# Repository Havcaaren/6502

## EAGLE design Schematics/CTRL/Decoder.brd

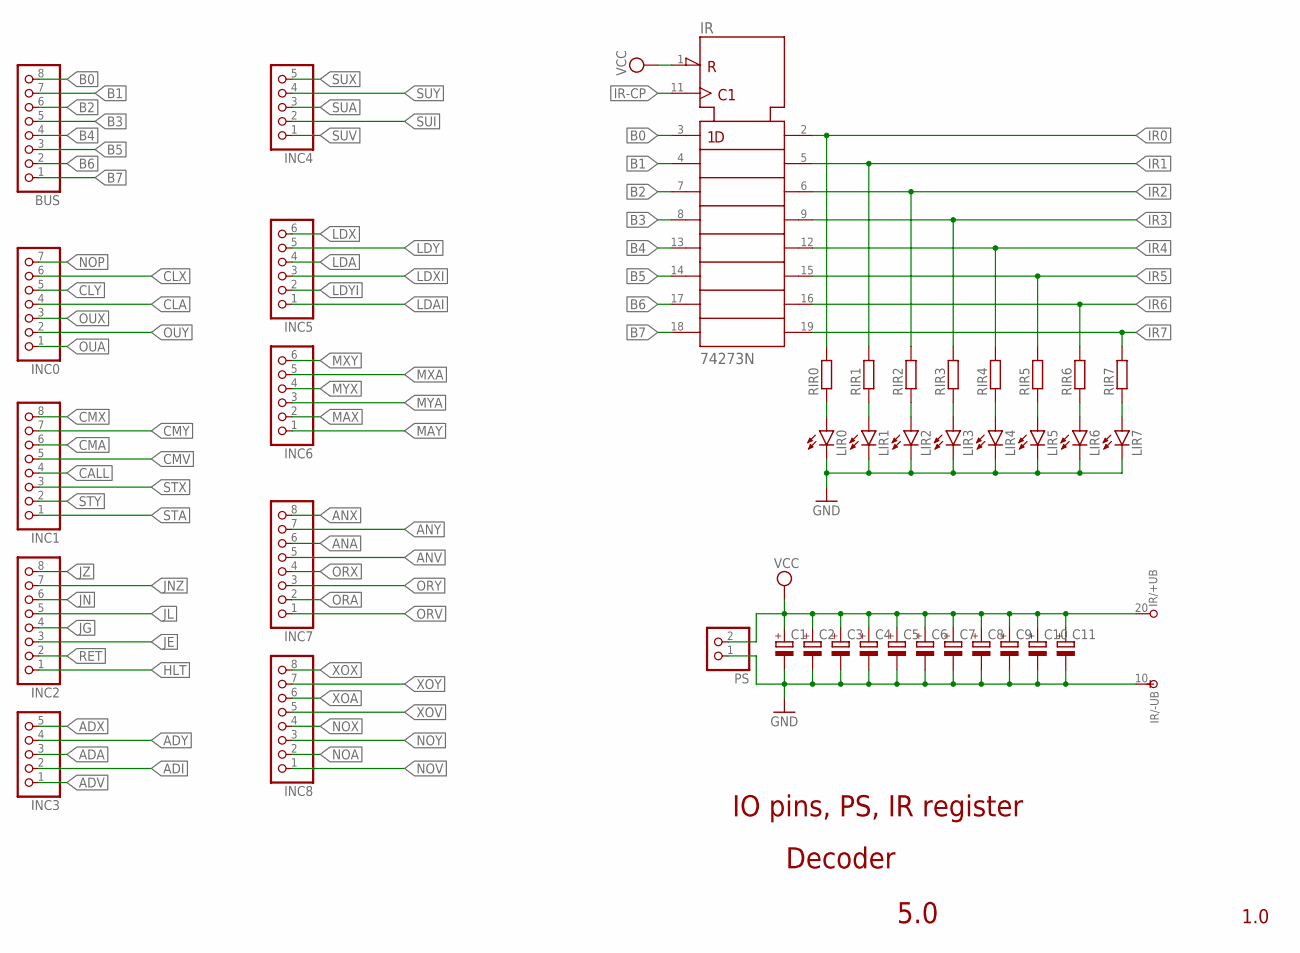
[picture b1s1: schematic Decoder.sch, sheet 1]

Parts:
BUS: PINHD-1X8; 1X08
C1, C2, C3, C4, C5, C6, C7, C8, C9, C10, C11: CPOL-EUE2.5-6; E2,5-6
INC0: PINHD-1X7; 1X07
INC1, INC2, INC7, INC8: PINHD-1X8; 1X08
INC3, INC4: PINHD-1X5; 1X05
INC5, INC6: PINHD-1X6; 1X06
IR: 74273N; DIL20
LIR0, LIR1, LIR2, LIR3, LIR4, LIR5, LIR6, LIR7: LED5MM
PS: PINHD-1X2; 1X02
RIR0, RIR1, RIR2, RIR3, RIR4, RIR5, RIR6, RIR7: R-EU_0204/7; 0204/7

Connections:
ADA: INC3.3; also elsewhere on the board
ADI: INC3.2; also elsewhere on the board
ADV: INC3.1; also elsewhere on the board
ADX: INC3.5; also elsewhere on the board
ADY: INC3.4; also elsewhere on the board
ANA: INC7.6; also elsewhere on the board
ANV: INC7.5; also elsewhere on the board
ANX: INC7.8; also elsewhere on the board
ANY: INC7.7; also elsewhere on the board
B0: BUS.8, IR.3 (1D)
B1: BUS.7, IR.4 (2D)
B2: BUS.6, IR.7 (3D)
B3: BUS.5, IR.8 (4D)
B4: BUS.4, IR.13 (5D)
B5: BUS.3, IR.14 (6D)
B6: BUS.2, IR.17 (7D)
B7: BUS.1, IR.18 (8D)
CALL: INC1.4; also elsewhere on the board
CLA: INC0.4; also elsewhere on the board
CLX: INC0.6; also elsewhere on the board
CLY: INC0.5; also elsewhere on the board
CMA: INC1.6; also elsewhere on the board
CMV: INC1.5; also elsewhere on the board
CMX: INC1.8; also elsewhere on the board
CMY: INC1.7; also elsewhere on the board
GND: C1.-, C2.-, C3.-, C4.-, C5.-, C6.-, C7.-, C8.-, C9.-, C10.-, C11.-, IR.10 (-UB), LIR0.K (C), LIR1.K (C), LIR2.K (C), LIR3.K (C), LIR4.K (C), LIR5.K (C), LIR6.K (C), LIR7.K (C), PS.1; also elsewhere on the board
HLT: INC2.1; also elsewhere on the board
IR0: IR.2 (1Q), RIR0.2; also elsewhere on the board
IR1: IR.5 (2Q), RIR1.2; also elsewhere on the board
IR2: IR.6 (3Q), RIR2.2; also elsewhere on the board
IR3: IR.9 (4Q), RIR3.2; also elsewhere on the board
IR4: IR.12 (5Q), RIR4.2; also elsewhere on the board
IR5: IR.15 (6Q), RIR5.2; also elsewhere on the board
IR6: IR.16 (7Q), RIR6.2; also elsewhere on the board
IR7: IR.19 (8Q), RIR7.2; also elsewhere on the board
IR-CP: IR.11 (CLK); also elsewhere on the board
JE: INC2.3; also elsewhere on the board
JG: INC2.4; also elsewhere on the board
JL: INC2.5; also elsewhere on the board
JN: INC2.6; also elsewhere on the board
JNZ: INC2.7; also elsewhere on the board
JZ: INC2.8; also elsewhere on the board
LDA: INC5.4; also elsewhere on the board
LDAI: INC5.1; also elsewhere on the board
LDX: INC5.6; also elsewhere on the board
LDXI: INC5.3; also elsewhere on the board
LDY: INC5.5; also elsewhere on the board
LDYI: INC5.2; also elsewhere on the board
MAX: INC6.2; also elsewhere on the board
MAY: INC6.1; also elsewhere on the board
MXA: INC6.5; also elsewhere on the board
MXY: INC6.6; also elsewhere on the board
MYA: INC6.3; also elsewhere on the board
MYX: INC6.4; also elsewhere on the board
unnamed: LIR0.A, RIR0.1
unnamed: LIR1.A, RIR1.1
unnamed: LIR2.A, RIR2.1
unnamed: LIR3.A, RIR3.1
unnamed: LIR4.A, RIR4.1
unnamed: LIR5.A, RIR5.1
unnamed: LIR6.A, RIR6.1
unnamed: LIR7.A, RIR7.1
NOA: INC8.2; also elsewhere on the board
NOP: INC0.7; also elsewhere on the board
NOV: INC8.1; also elsewhere on the board
NOX: INC8.4; also elsewhere on the board
NOY: INC8.3; also elsewhere on the board
ORA: INC7.2; also elsewhere on the board
ORV: INC7.1; also elsewhere on the board
ORX: INC7.4; also elsewhere on the board
ORY: INC7.3; also elsewhere on the board
OUA: INC0.1; also elsewhere on the board
OUX: INC0.3; also elsewhere on the board
OUY: INC0.2; also elsewhere on the board
RET: INC2.2; also elsewhere on the board
STA: INC1.1; also elsewhere on the board
STX: INC1.3; also elsewhere on the board
STY: INC1.2; also elsewhere on the board
SUA: INC4.3; also elsewhere on the board
SUI: INC4.2; also elsewhere on the board
SUV: INC4.1; also elsewhere on the board
SUX: INC4.5; also elsewhere on the board
SUY: INC4.4; also elsewhere on the board
VCC: C1.+, C2.+, C3.+, C4.+, C5.+, C6.+, C7.+, C8.+, C9.+, C10.+, C11.+, IR.1 (!CLR), IR.20 (+UB), PS.2; also elsewhere on the board
XOA: INC8.6; also elsewhere on the board
XOV: INC8.5; also elsewhere on the board
XOX: INC8.8; also elsewhere on the board
XOY: INC8.7; also elsewhere on the board

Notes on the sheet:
1.0
5.0
Decoder
IO pins, PS, IR register

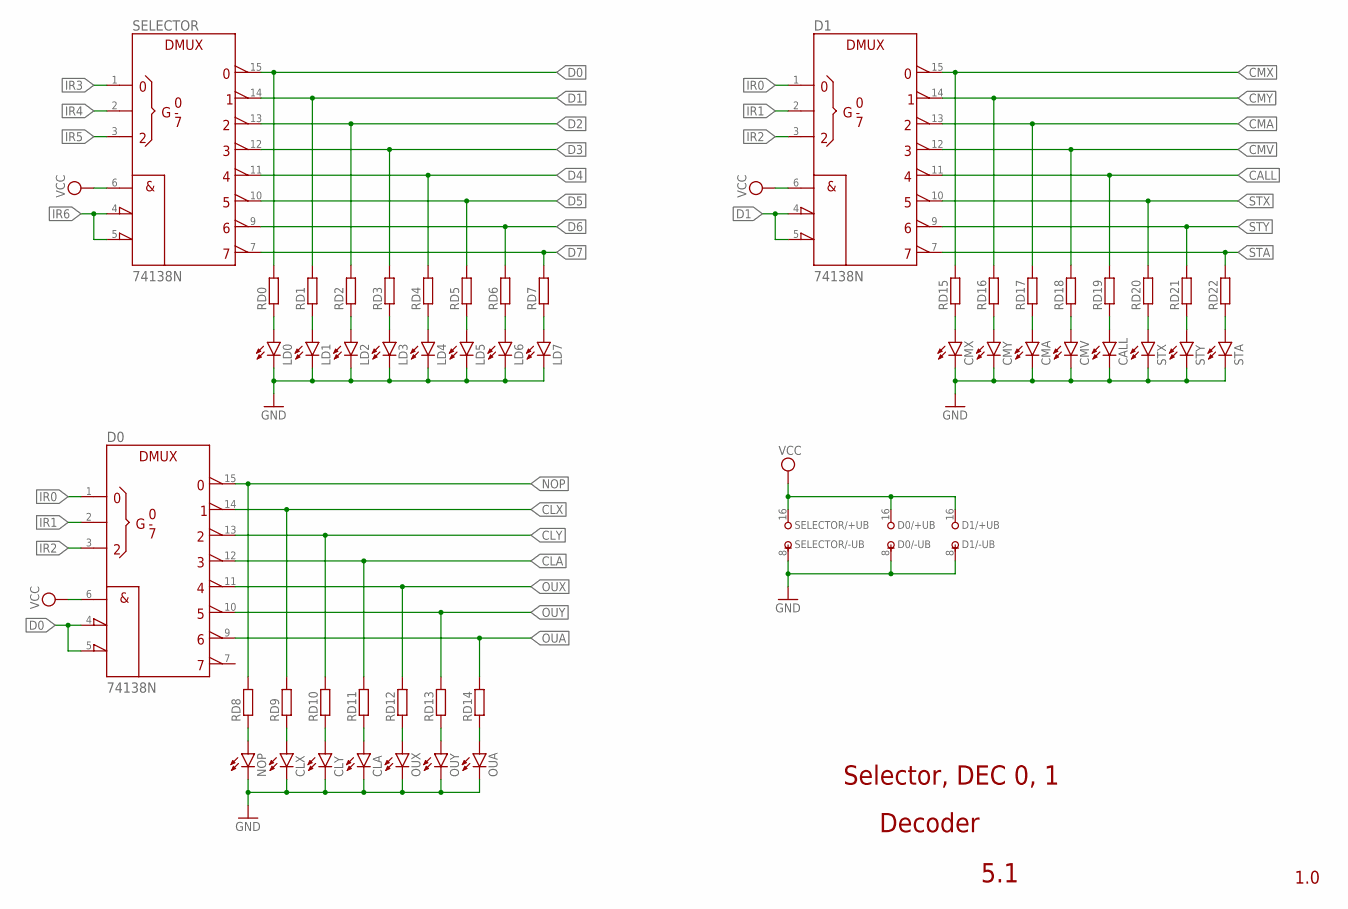
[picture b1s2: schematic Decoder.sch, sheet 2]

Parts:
CALL: LED5MM
CLA: LED5MM
CLX: LED5MM
CLY: LED5MM
CMA: LED5MM
CMV: LED5MM
CMX: LED5MM
CMY: LED5MM
D0, D1: 74138N; DIL16
LD0, LD1, LD2, LD3, LD4, LD5, LD6, LD7: LED5MM
NOP: LED5MM
OUA: LED5MM
OUX: LED5MM
OUY: LED5MM
RD0, RD1, RD2, RD3, RD4, RD5, RD6, RD7, RD8, RD9, RD10, RD11, RD12, RD13, RD14, RD15, RD16, RD17, RD18, RD19, RD20, RD21, RD22: R-EU_0204/7; 0204/7
SELECTOR: 74138N; DIL16
STA: LED5MM
STX: LED5MM
STY: LED5MM

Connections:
CALL: D1.11 (Y4), RD19.2; also elsewhere on the board
CLA: D0.12 (Y3), RD11.2; also elsewhere on the board
CLX: D0.14 (Y1), RD9.2; also elsewhere on the board
CLY: D0.13 (Y2), RD10.2; also elsewhere on the board
CMA: D1.13 (Y2), RD17.2; also elsewhere on the board
CMV: D1.12 (Y3), RD18.2; also elsewhere on the board
CMX: D1.15 (Y0), RD15.2; also elsewhere on the board
CMY: D1.14 (Y1), RD16.2; also elsewhere on the board
D0: D0.4 (!G2A), D0.5 (!G2B), RD0.2, SELECTOR.15 (Y0)
D1: D1.4 (!G2A), D1.5 (!G2B), RD1.2, SELECTOR.14 (Y1)
D2: RD2.2, SELECTOR.13 (Y2); also elsewhere on the board
D3: RD3.2, SELECTOR.12 (Y3); also elsewhere on the board
D4: RD4.2, SELECTOR.11 (Y4); also elsewhere on the board
D5: RD5.2, SELECTOR.10 (Y5); also elsewhere on the board
D6: RD6.2, SELECTOR.9 (Y6); also elsewhere on the board
D7: RD7.2, SELECTOR.7 (Y7); also elsewhere on the board
GND: CALL.K (C), CLA.K (C), CLX.K (C), CLY.K (C), CMA.K (C), CMV.K (C), CMX.K (C), CMY.K (C), D0.8 (-UB), D1.8 (-UB), LD0.K (C), LD1.K (C), LD2.K (C), LD3.K (C), LD4.K (C), LD5.K (C), LD6.K (C), LD7.K (C), NOP.K (C), OUA.K (C), OUX.K (C), OUY.K (C), SELECTOR.8 (-UB), STA.K (C), STX.K (C), STY.K (C); also elsewhere on the board
IR0: D0.1 (A), D1.1 (A); also elsewhere on the board
IR1: D0.2 (B), D1.2 (B); also elsewhere on the board
IR2: D0.3 (C), D1.3 (C); also elsewhere on the board
IR3: SELECTOR.1 (A); also elsewhere on the board
IR4: SELECTOR.2 (B); also elsewhere on the board
IR5: SELECTOR.3 (C); also elsewhere on the board
IR6: SELECTOR.4 (!G2A), SELECTOR.5 (!G2B); also elsewhere on the board
unnamed: LD0.A, RD0.1
unnamed: LD1.A, RD1.1
unnamed: LD2.A, RD2.1
unnamed: LD3.A, RD3.1
unnamed: LD4.A, RD4.1
unnamed: LD5.A, RD5.1
unnamed: LD6.A, RD6.1
unnamed: LD7.A, RD7.1
unnamed: CMX.A, RD15.1
unnamed: CMY.A, RD16.1
unnamed: CMA.A, RD17.1
unnamed: CMV.A, RD18.1
unnamed: CALL.A, RD19.1
unnamed: RD20.1, STX.A
unnamed: RD21.1, STY.A
unnamed: RD22.1, STA.A
unnamed: NOP.A, RD8.1
unnamed: CLX.A, RD9.1
unnamed: CLY.A, RD10.1
unnamed: CLA.A, RD11.1
unnamed: OUX.A, RD12.1
unnamed: OUY.A, RD13.1
unnamed: OUA.A, RD14.1
NOP: D0.15 (Y0), RD8.2; also elsewhere on the board
OUA: D0.9 (Y6), RD14.2; also elsewhere on the board
OUX: D0.11 (Y4), RD12.2; also elsewhere on the board
OUY: D0.10 (Y5), RD13.2; also elsewhere on the board
STA: D1.7 (Y7), RD22.2; also elsewhere on the board
STX: D1.10 (Y5), RD20.2; also elsewhere on the board
STY: D1.9 (Y6), RD21.2; also elsewhere on the board
VCC: D0.6 (G1), D0.16 (+UB), D1.6 (G1), D1.16 (+UB), SELECTOR.6 (G1), SELECTOR.16 (+UB); also elsewhere on the board

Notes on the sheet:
Decoder
5.1
1.0
Selector, DEC 0, 1

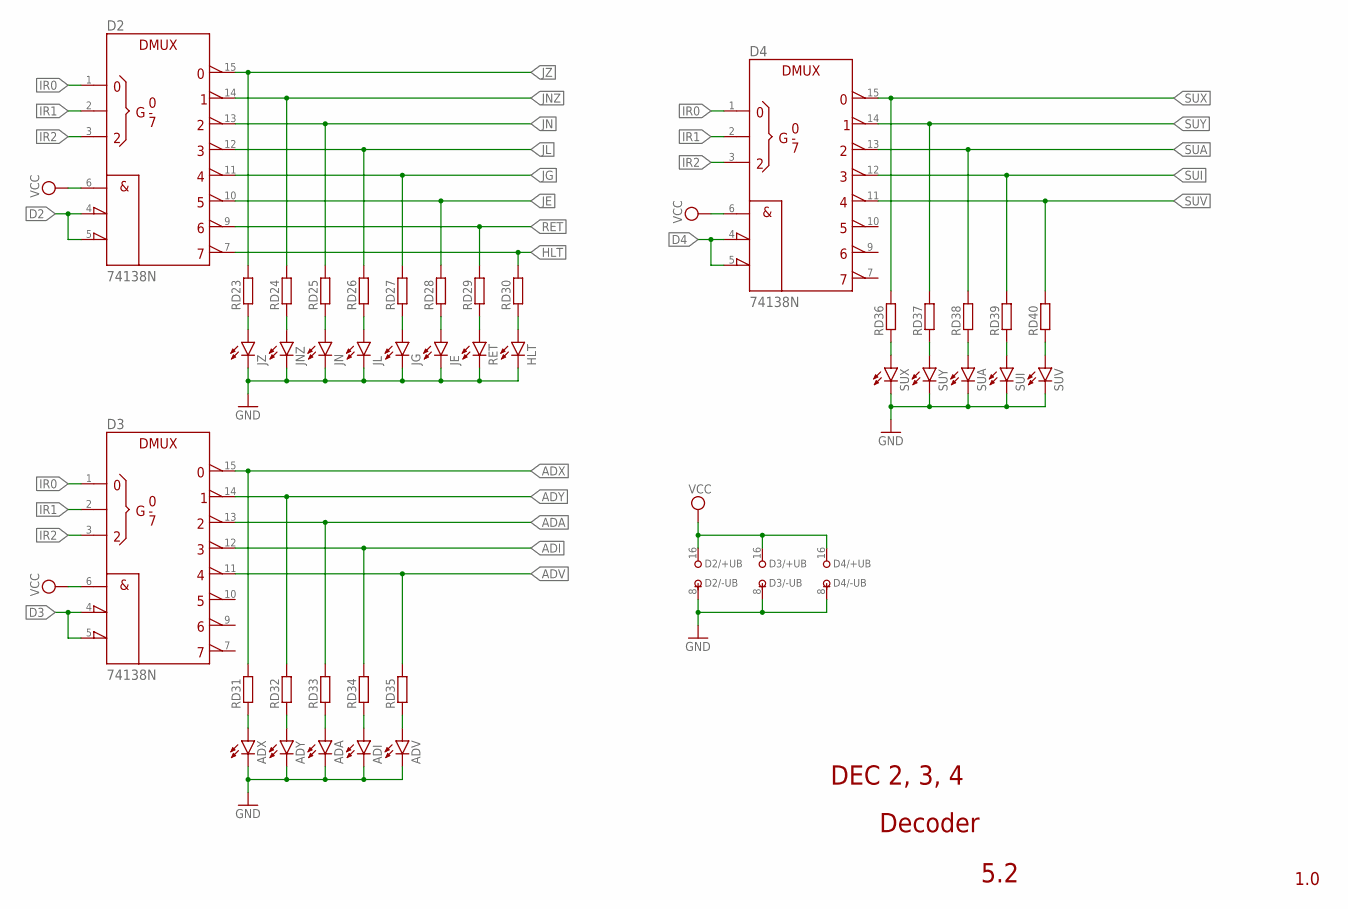
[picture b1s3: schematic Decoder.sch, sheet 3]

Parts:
ADA: LED5MM
ADI: LED5MM
ADV: LED5MM
ADX: LED5MM
ADY: LED5MM
D2, D3, D4: 74138N; DIL16
HLT: LED5MM
JE: LED5MM
JG: LED5MM
JL: LED5MM
JN: LED5MM
JNZ: LED5MM
JZ: LED5MM
RD23, RD24, RD25, RD26, RD27, RD28, RD29, RD30, RD31, RD32, RD33, RD34, RD35, RD36, RD37, RD38, RD39, RD40: R-EU_0204/7; 0204/7
RET: LED5MM
SUA: LED5MM
SUI: LED5MM
SUV: LED5MM
SUX: LED5MM
SUY: LED5MM

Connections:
ADA: D3.13 (Y2), RD33.2; also elsewhere on the board
ADI: D3.12 (Y3), RD34.2; also elsewhere on the board
ADV: D3.11 (Y4), RD35.2; also elsewhere on the board
ADX: D3.15 (Y0), RD31.2; also elsewhere on the board
ADY: D3.14 (Y1), RD32.2; also elsewhere on the board
D2: D2.4 (!G2A), D2.5 (!G2B); also elsewhere on the board
D3: D3.4 (!G2A), D3.5 (!G2B); also elsewhere on the board
D4: D4.4 (!G2A), D4.5 (!G2B); also elsewhere on the board
GND: ADA.K (C), ADI.K (C), ADV.K (C), ADX.K (C), ADY.K (C), D2.8 (-UB), D3.8 (-UB), D4.8 (-UB), HLT.K (C), JE.K (C), JG.K (C), JL.K (C), JN.K (C), JNZ.K (C), JZ.K (C), RET.K (C), SUA.K (C), SUI.K (C), SUV.K (C), SUX.K (C), SUY.K (C); also elsewhere on the board
HLT: D2.7 (Y7), RD30.2; also elsewhere on the board
IR0: D2.1 (A), D3.1 (A), D4.1 (A); also elsewhere on the board
IR1: D2.2 (B), D3.2 (B), D4.2 (B); also elsewhere on the board
IR2: D2.3 (C), D3.3 (C), D4.3 (C); also elsewhere on the board
JE: D2.10 (Y5), RD28.2; also elsewhere on the board
JG: D2.11 (Y4), RD27.2; also elsewhere on the board
JL: D2.12 (Y3), RD26.2; also elsewhere on the board
JN: D2.13 (Y2), RD25.2; also elsewhere on the board
JNZ: D2.14 (Y1), RD24.2; also elsewhere on the board
JZ: D2.15 (Y0), RD23.2; also elsewhere on the board
unnamed: JZ.A, RD23.1
unnamed: JNZ.A, RD24.1
unnamed: JN.A, RD25.1
unnamed: JL.A, RD26.1
unnamed: JG.A, RD27.1
unnamed: JE.A, RD28.1
unnamed: RD29.1, RET.A
unnamed: HLT.A, RD30.1
unnamed: ADX.A, RD31.1
unnamed: ADY.A, RD32.1
unnamed: ADA.A, RD33.1
unnamed: ADI.A, RD34.1
unnamed: ADV.A, RD35.1
unnamed: RD36.1, SUX.A
unnamed: RD37.1, SUY.A
unnamed: RD38.1, SUA.A
unnamed: RD39.1, SUI.A
unnamed: RD40.1, SUV.A
RET: D2.9 (Y6), RD29.2; also elsewhere on the board
SUA: D4.13 (Y2), RD38.2; also elsewhere on the board
SUI: D4.12 (Y3), RD39.2; also elsewhere on the board
SUV: D4.11 (Y4), RD40.2; also elsewhere on the board
SUX: D4.15 (Y0), RD36.2; also elsewhere on the board
SUY: D4.14 (Y1), RD37.2; also elsewhere on the board
VCC: D2.6 (G1), D2.16 (+UB), D3.6 (G1), D3.16 (+UB), D4.6 (G1), D4.16 (+UB); also elsewhere on the board

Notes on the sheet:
Decoder
5.2
1.0
DEC 2, 3, 4

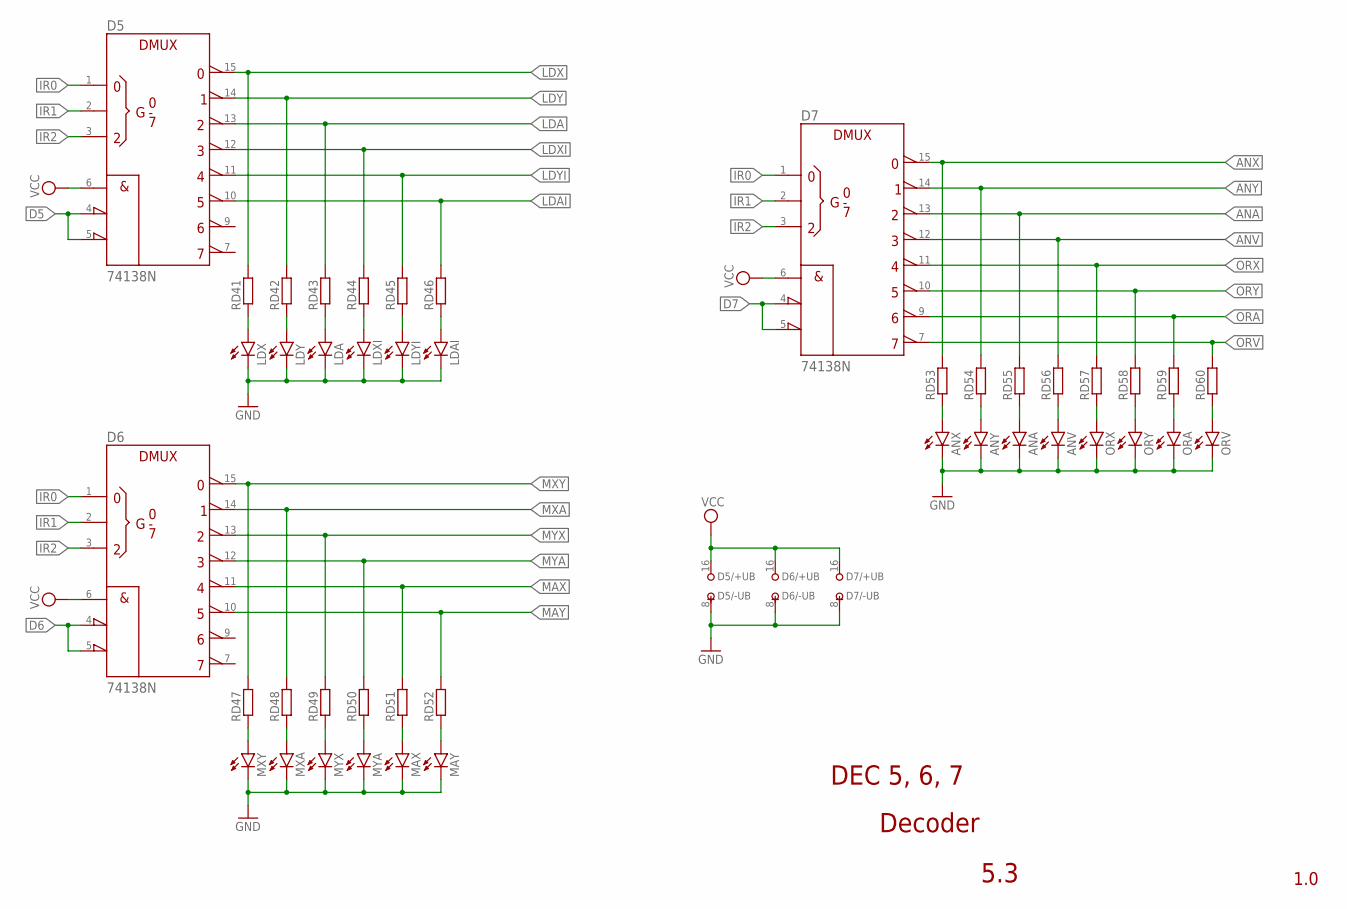
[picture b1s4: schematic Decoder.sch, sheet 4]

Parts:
ANA: LED5MM
ANV: LED5MM
ANX: LED5MM
ANY: LED5MM
D5, D6, D7: 74138N; DIL16
LDA: LED5MM
LDAI: LED5MM
LDX: LED5MM
LDXI: LED5MM
LDY: LED5MM
LDYI: LED5MM
MAX: LED5MM
MAY: LED5MM
MXA: LED5MM
MXY: LED5MM
MYA: LED5MM
MYX: LED5MM
ORA: LED5MM
ORV: LED5MM
ORX: LED5MM
ORY: LED5MM
RD41, RD42, RD43, RD44, RD45, RD46, RD47, RD48, RD49, RD50, RD51, RD52, RD53, RD54, RD55, RD56, RD57, RD58, RD59, RD60: R-EU_0204/7; 0204/7

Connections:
ANA: D7.13 (Y2), RD55.2; also elsewhere on the board
ANV: D7.12 (Y3), RD56.2; also elsewhere on the board
ANX: D7.15 (Y0), RD53.2; also elsewhere on the board
ANY: D7.14 (Y1), RD54.2; also elsewhere on the board
D5: D5.4 (!G2A), D5.5 (!G2B); also elsewhere on the board
D6: D6.4 (!G2A), D6.5 (!G2B); also elsewhere on the board
D7: D7.4 (!G2A), D7.5 (!G2B); also elsewhere on the board
GND: ANA.K (C), ANV.K (C), ANX.K (C), ANY.K (C), D5.8 (-UB), D6.8 (-UB), D7.8 (-UB), LDA.K (C), LDAI.K (C), LDX.K (C), LDXI.K (C), LDY.K (C), LDYI.K (C), MAX.K (C), MAY.K (C), MXA.K (C), MXY.K (C), MYA.K (C), MYX.K (C), ORA.K (C), ORV.K (C), ORX.K (C), ORY.K (C); also elsewhere on the board
IR0: D5.1 (A), D6.1 (A), D7.1 (A); also elsewhere on the board
IR1: D5.2 (B), D6.2 (B), D7.2 (B); also elsewhere on the board
IR2: D5.3 (C), D6.3 (C), D7.3 (C); also elsewhere on the board
LDA: D5.13 (Y2), RD43.2; also elsewhere on the board
LDAI: D5.10 (Y5), RD46.2; also elsewhere on the board
LDX: D5.15 (Y0), RD41.2; also elsewhere on the board
LDXI: D5.12 (Y3), RD44.2; also elsewhere on the board
LDY: D5.14 (Y1), RD42.2; also elsewhere on the board
LDYI: D5.11 (Y4), RD45.2; also elsewhere on the board
MAX: D6.11 (Y4), RD51.2; also elsewhere on the board
MAY: D6.10 (Y5), RD52.2; also elsewhere on the board
MXA: D6.14 (Y1), RD48.2; also elsewhere on the board
MXY: D6.15 (Y0), RD47.2; also elsewhere on the board
MYA: D6.12 (Y3), RD50.2; also elsewhere on the board
MYX: D6.13 (Y2), RD49.2; also elsewhere on the board
unnamed: LDX.A, RD41.1
unnamed: LDY.A, RD42.1
unnamed: LDA.A, RD43.1
unnamed: LDXI.A, RD44.1
unnamed: LDYI.A, RD45.1
unnamed: LDAI.A, RD46.1
unnamed: MXY.A, RD47.1
unnamed: MXA.A, RD48.1
unnamed: MYX.A, RD49.1
unnamed: MYA.A, RD50.1
unnamed: MAX.A, RD51.1
unnamed: MAY.A, RD52.1
unnamed: ANX.A, RD53.1
unnamed: ANY.A, RD54.1
unnamed: ANA.A, RD55.1
unnamed: ANV.A, RD56.1
unnamed: ORX.A, RD57.1
unnamed: ORY.A, RD58.1
unnamed: ORA.A, RD59.1
unnamed: ORV.A, RD60.1
ORA: D7.9 (Y6), RD59.2; also elsewhere on the board
ORV: D7.7 (Y7), RD60.2; also elsewhere on the board
ORX: D7.11 (Y4), RD57.2; also elsewhere on the board
ORY: D7.10 (Y5), RD58.2; also elsewhere on the board
VCC: D5.6 (G1), D5.16 (+UB), D6.6 (G1), D6.16 (+UB), D7.6 (G1), D7.16 (+UB); also elsewhere on the board

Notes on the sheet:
Decoder
5.3
1.0
DEC 5, 6, 7

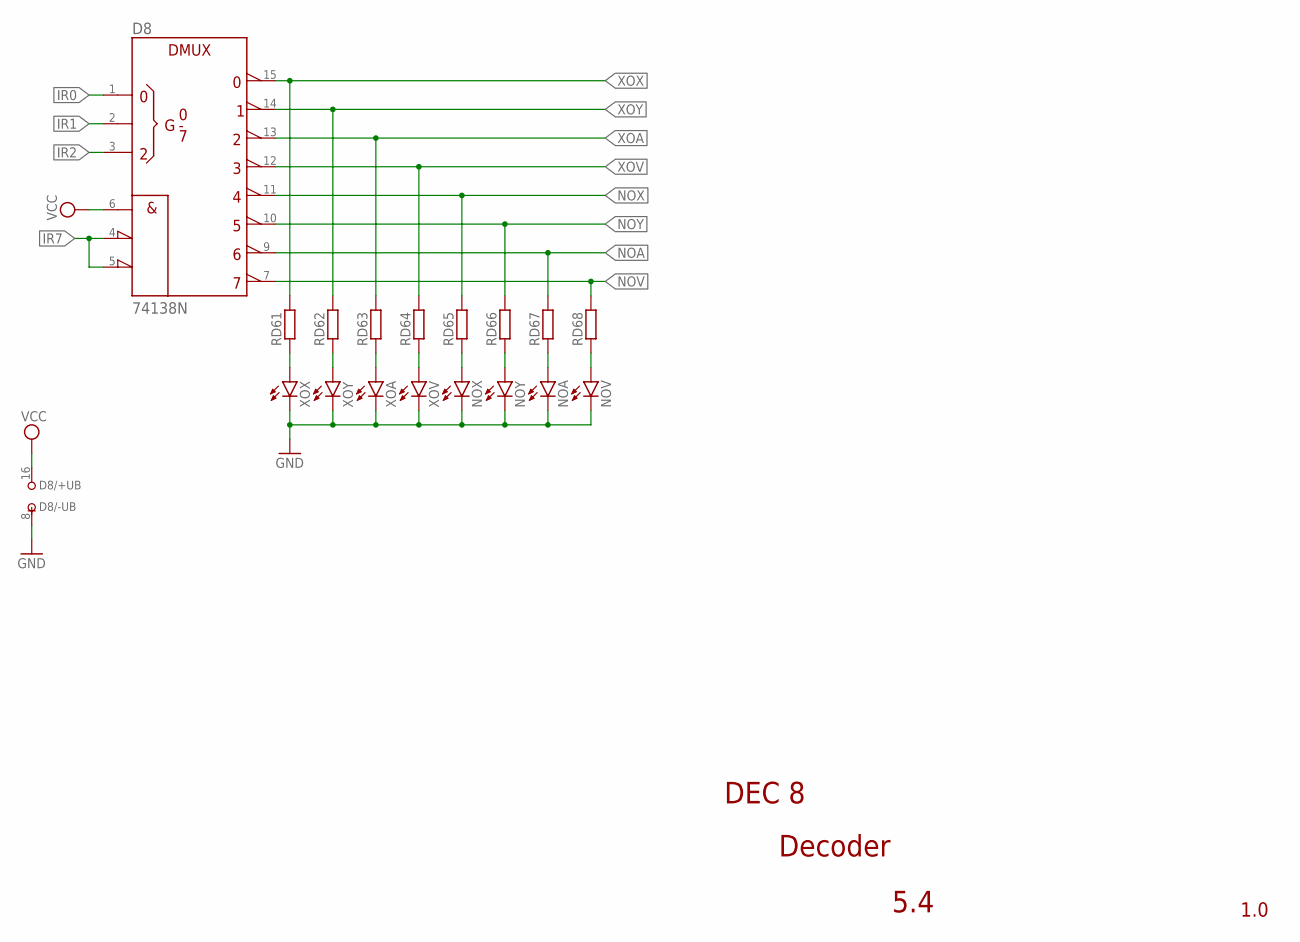
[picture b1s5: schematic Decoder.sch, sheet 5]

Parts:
D8: 74138N; DIL16
NOA: LED5MM
NOV: LED5MM
NOX: LED5MM
NOY: LED5MM
RD61, RD62, RD63, RD64, RD65, RD66, RD67, RD68: R-EU_0204/7; 0204/7
XOA: LED5MM
XOV: LED5MM
XOX: LED5MM
XOY: LED5MM

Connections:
GND: D8.8 (-UB), NOA.K (C), NOV.K (C), NOX.K (C), NOY.K (C), XOA.K (C), XOV.K (C), XOX.K (C), XOY.K (C); also elsewhere on the board
IR0: D8.1 (A); also elsewhere on the board
IR1: D8.2 (B); also elsewhere on the board
IR2: D8.3 (C); also elsewhere on the board
IR7: D8.4 (!G2A), D8.5 (!G2B); also elsewhere on the board
unnamed: RD61.1, XOX.A
unnamed: RD62.1, XOY.A
unnamed: RD63.1, XOA.A
unnamed: RD64.1, XOV.A
unnamed: NOX.A, RD65.1
unnamed: NOY.A, RD66.1
unnamed: NOA.A, RD67.1
unnamed: NOV.A, RD68.1
NOA: D8.9 (Y6), RD67.2; also elsewhere on the board
NOV: D8.7 (Y7), RD68.2; also elsewhere on the board
NOX: D8.11 (Y4), RD65.2; also elsewhere on the board
NOY: D8.10 (Y5), RD66.2; also elsewhere on the board
VCC: D8.6 (G1), D8.16 (+UB); also elsewhere on the board
XOA: D8.13 (Y2), RD63.2; also elsewhere on the board
XOV: D8.12 (Y3), RD64.2; also elsewhere on the board
XOX: D8.15 (Y0), RD61.2; also elsewhere on the board
XOY: D8.14 (Y1), RD62.2; also elsewhere on the board

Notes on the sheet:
Decoder
5.4
1.0
DEC 8

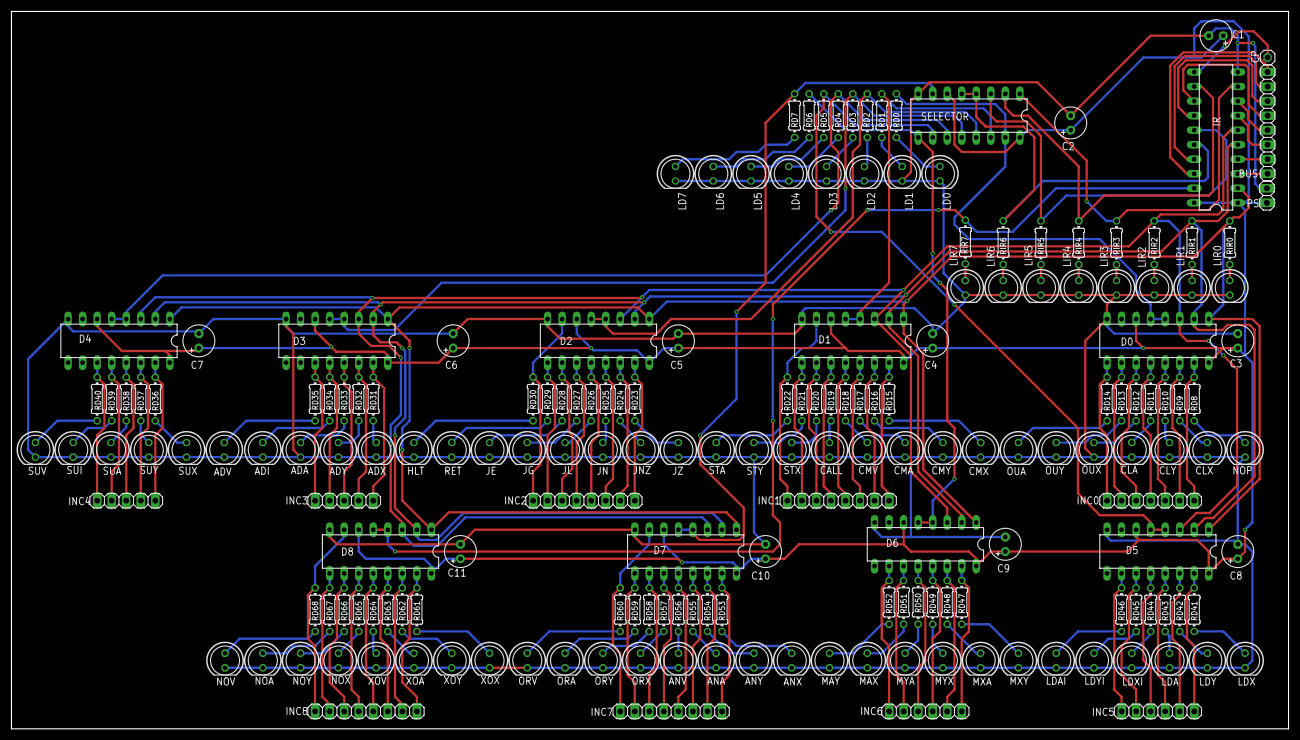
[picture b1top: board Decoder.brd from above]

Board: 2 copper layers, 223.2 x 125.4 mm, 188 parts (0 on the bottom side), 165 nets.

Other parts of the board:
CP: 1X01

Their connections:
IR-CP: CP.1; also elsewhere on the board

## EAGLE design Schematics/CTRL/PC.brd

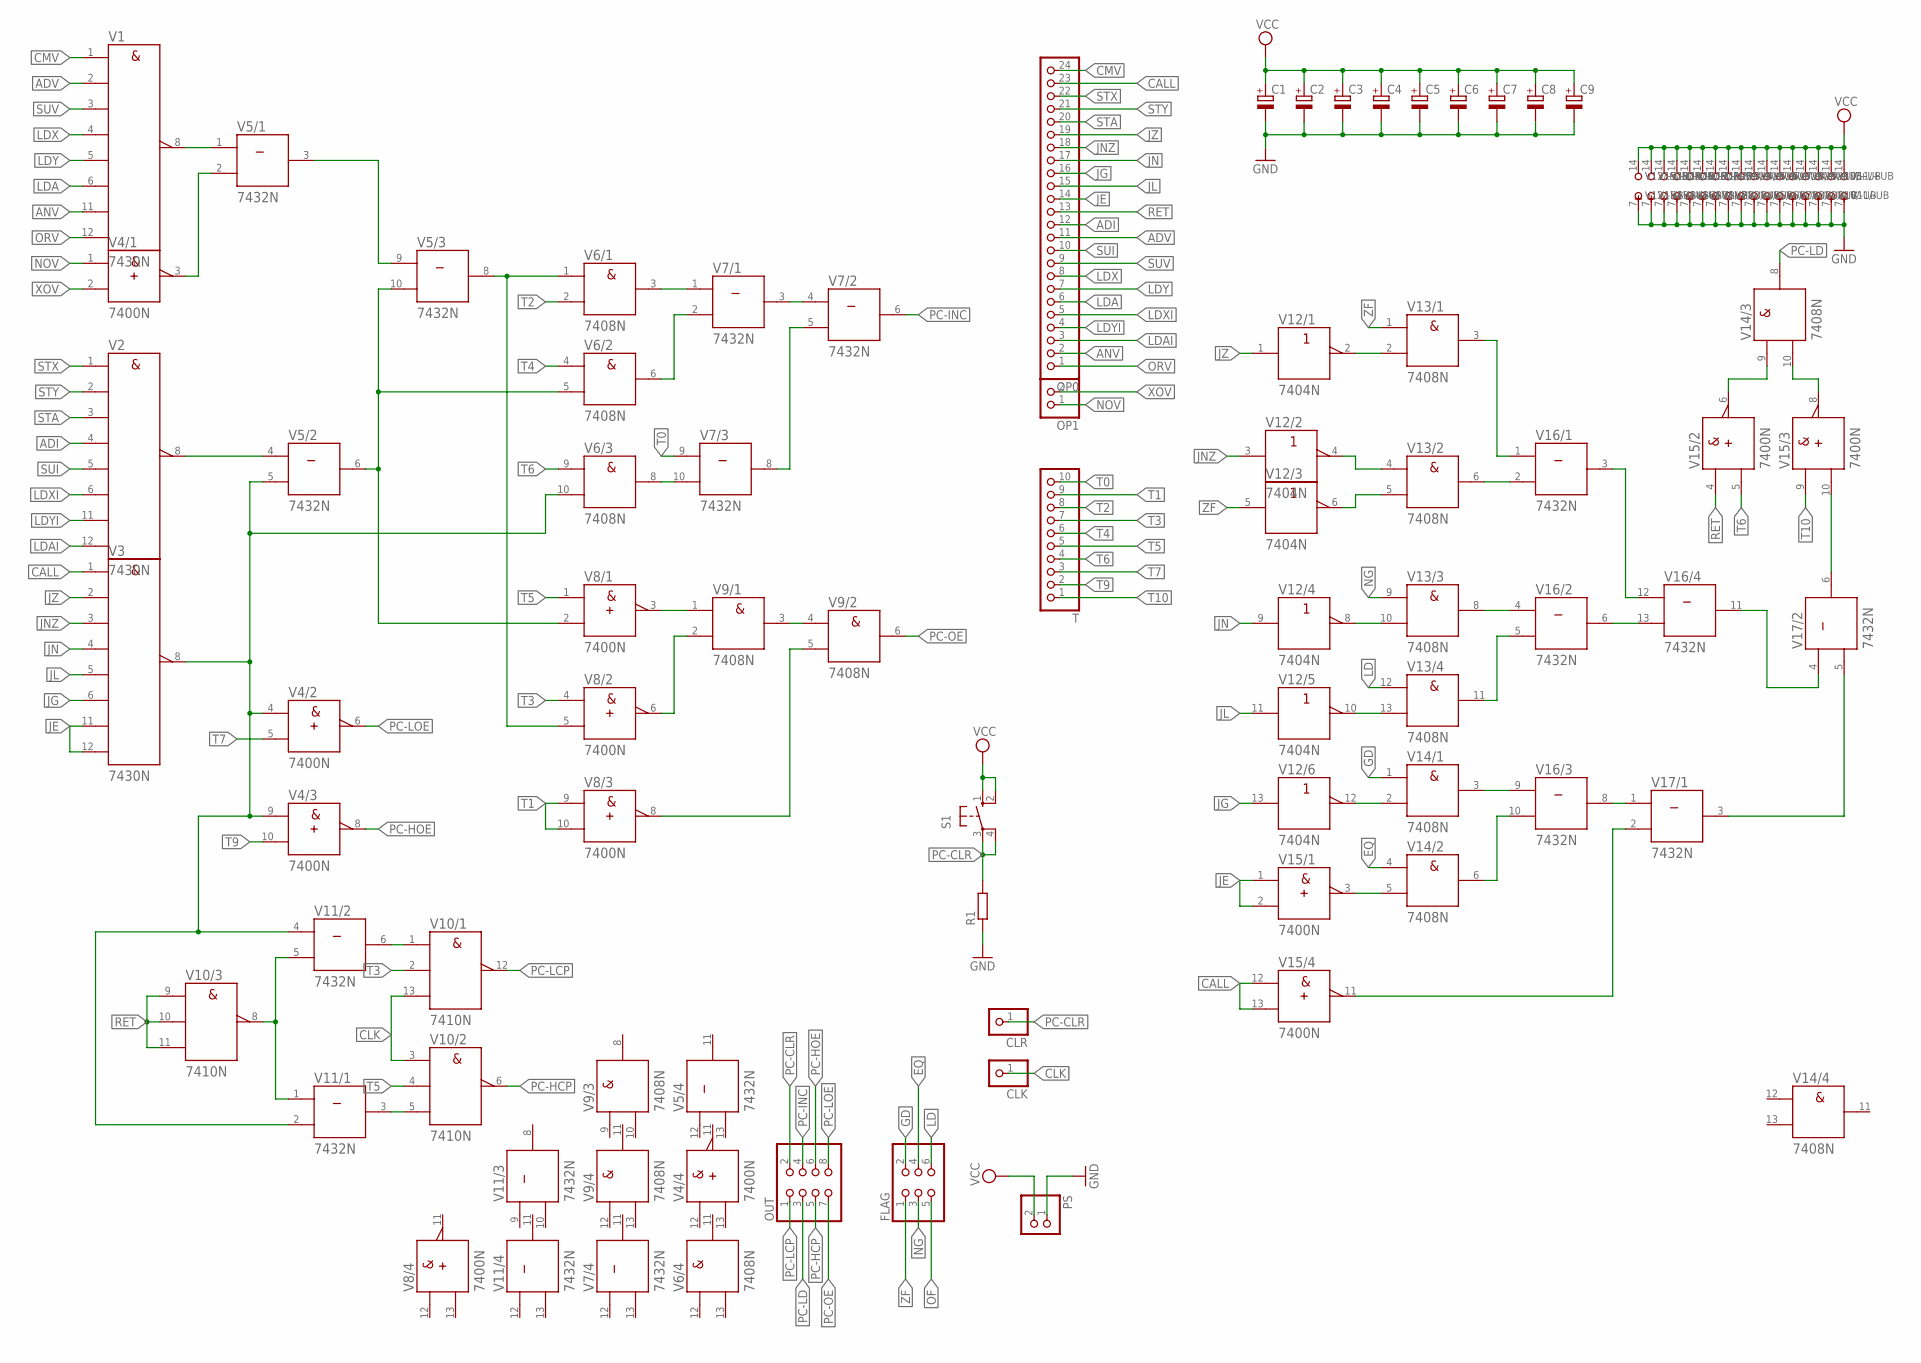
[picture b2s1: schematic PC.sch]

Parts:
C1, C2, C3, C4, C5, C6, C7, C8, C9: CPOL-EUE2.5-6; E2,5-6
CLK: PINHD-1X1; 1X01
CLR: PINHD-1X1; 1X01
FLAG: PINHD-2X3; 2X03
OP0: PINHD-1X24; 1X24
OP1: PINHD-1X2; 1X02
OUT: PINHD-2X4; 2X04
PS: PINHD-1X2; 1X02
R1: R-EU_0207/7; 0207/7
S1: 10-XX; B3F-10XX
T: PINHD-1X10; 1X10
V1, V2, V3: 7430N; DIL14
V4, V8, V15: 7400N; DIL14
V5, V7, V11, V16, V17: 7432N; DIL14
V6, V9, V13, V14: 7408N; DIL14
V10: 7410N; DIL14
V12: 7404N; DIL14

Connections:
ADI: OP0.12, V2.4 (D)
ADV: OP0.11, V1.2 (B)
ANV: OP0.2, V1.11 (G)
CALL: OP0.23, V3.1 (A), V15.12 (A), V15.13 (B)
CLK: CLK.1, V10.3 (A), V10.13 (C)
CMV: OP0.24, V1.1 (A)
EQ: FLAG.4, V14.4 (A)
GD: FLAG.2, V14.1 (A)
GND: C1.-, C2.-, C3.-, C4.-, C5.-, C6.-, C7.-, C8.-, C9.-, PS.1, R1.1, V1.7 (-UB), V2.7 (-UB), V3.7 (-UB), V4.7 (-UB), V5.7 (-UB), V6.7 (-UB), V7.7 (-UB), V8.7 (-UB), V9.7 (-UB), V10.7 (-UB), V11.7 (-UB), V12.7 (-UB), V13.7 (-UB), V14.7 (-UB), V15.7 (-UB), V16.7 (-UB), V17.7 (-UB)
JE: OP0.14, V3.11 (G), V3.12 (H), V15.1 (A), V15.2 (B)
JG: OP0.16, V3.6 (F), V12.13 (A)
JL: OP0.15, V3.5 (E), V12.11 (A)
JN: OP0.17, V3.4 (D), V12.9 (A)
JNZ: OP0.18, V3.3 (C), V12.3 (A)
JZ: OP0.19, V3.2 (B), V12.1 (A)
LD: FLAG.6, V13.12 (A)
LDA: OP0.6, V1.6 (F)
LDAI: OP0.3, V2.12 (H)
LDX: OP0.8, V1.4 (D)
LDXI: OP0.5, V2.6 (F)
LDY: OP0.7, V1.5 (E)
LDYI: OP0.4, V2.11 (G)
unnamed: V12.2 (Y), V13.2 (B)
unnamed: V13.3 (Y), V16.1 (A)
unnamed: V12.4 (Y), V13.4 (A)
unnamed: V10.5 (C), V11.3 (Y)
unnamed: V12.6 (Y), V13.5 (B)
unnamed: V13.6 (Y), V16.2 (B)
unnamed: V10.1 (A), V11.6 (Y)
unnamed: V10.8 (Y), V11.1 (A), V11.5 (B)
unnamed: V12.8 (Y), V13.10 (B)
unnamed: V12.10 (Y), V13.13 (B)
unnamed: V13.8 (Y), V16.4 (A)
unnamed: V13.11 (Y), V16.5 (B)
unnamed: V14.6 (Y), V16.10 (B)
unnamed: V12.12 (Y), V14.2 (B)
unnamed: V14.3 (Y), V16.9 (A)
unnamed: V14.5 (B), V15.3 (Y)
unnamed: V5.6 (Y), V5.10 (B), V6.5 (B), V8.2 (B)
unnamed: V6.6 (Y), V7.2 (B)
unnamed: V5.8 (Y), V6.1 (A), V8.5 (B)
unnamed: V6.3 (Y), V7.1 (A)
unnamed: V7.5 (B), V7.8 (Y)
unnamed: V4.3 (Y), V5.2 (B)
unnamed: V5.3 (Y), V5.9 (A)
unnamed: V7.3 (Y), V7.4 (A)
unnamed: V1.8 (Y), V5.1 (A)
unnamed: V2.8 (Y), V5.4 (A)
unnamed: V3.8 (Y), V4.4 (A), V4.9 (A), V5.5 (B), V6.10 (B), V11.2 (B), V11.4 (A)
unnamed: V16.6 (Y), V16.13 (B)
unnamed: V6.8 (Y), V7.10 (B)
unnamed: V16.3 (Y), V16.12 (A)
unnamed: V16.8 (Y), V17.1 (A)
unnamed: V8.3 (Y), V9.1 (A)
unnamed: V8.6 (Y), V9.2 (B)
unnamed: V8.8 (Y), V9.5 (B)
unnamed: V9.3 (Y), V9.4 (A)
unnamed: V15.11 (Y), V17.2 (B)
unnamed: V14.10 (B), V15.8 (Y)
unnamed: V14.9 (A), V15.6 (Y)
unnamed: V15.10 (B), V17.6 (Y)
unnamed: V16.11 (Y), V17.4 (A)
unnamed: V17.3 (Y), V17.5 (B)
NG: FLAG.3, V13.9 (A)
NOV: OP1.1, V4.1 (A)
OF: FLAG.5
ORV: OP0.1, V1.12 (H)
PC-CLR: CLR.1, OUT.2, R1.2, S1.3, S1.4 (P1)
PC-HCP: OUT.5, V10.6 (Y)
PC-HOE: OUT.6, V4.8 (Y)
PC-INC: OUT.4, V7.6 (Y)
PC-LCP: OUT.1, V10.12 (Y)
PC-LD: OUT.3, V14.8 (Y)
PC-LOE: OUT.8, V4.6 (Y)
PC-OE: OUT.7, V9.6 (Y)
RET: OP0.13, V10.9 (A), V10.10 (B), V10.11 (C), V15.4 (A)
STA: OP0.20, V2.3 (C)
STX: OP0.22, V2.1 (A)
STY: OP0.21, V2.2 (B)
SUI: OP0.10, V2.5 (E)
SUV: OP0.9, V1.3 (C)
T0: T.10, V7.9 (A)
T1: T.9, V8.9 (A), V8.10 (B)
T2: T.8, V6.2 (B)
T3: T.7, V8.4 (A), V10.2 (B)
T4: T.6, V6.4 (A)
T5: T.5, V8.1 (A), V10.4 (B)
T6: T.4, V6.9 (A), V15.5 (B)
T7: T.3, V4.5 (B)
T9: T.2, V4.10 (B)
T10: T.1, V15.9 (A)
VCC: C1.+, C2.+, C3.+, C4.+, C5.+, C6.+, C7.+, C8.+, C9.+, PS.2, S1.1 (S), S1.2 (S1), V1.14 (+UB), V2.14 (+UB), V3.14 (+UB), V4.14 (+UB), V5.14 (+UB), V6.14 (+UB), V7.14 (+UB), V8.14 (+UB), V9.14 (+UB), V10.14 (+UB), V11.14 (+UB), V12.14 (+UB), V13.14 (+UB), V14.14 (+UB), V15.14 (+UB), V16.14 (+UB), V17.14 (+UB)
XOV: OP1.2, V4.2 (B)
ZF: FLAG.1, V12.5 (A), V13.1 (A)

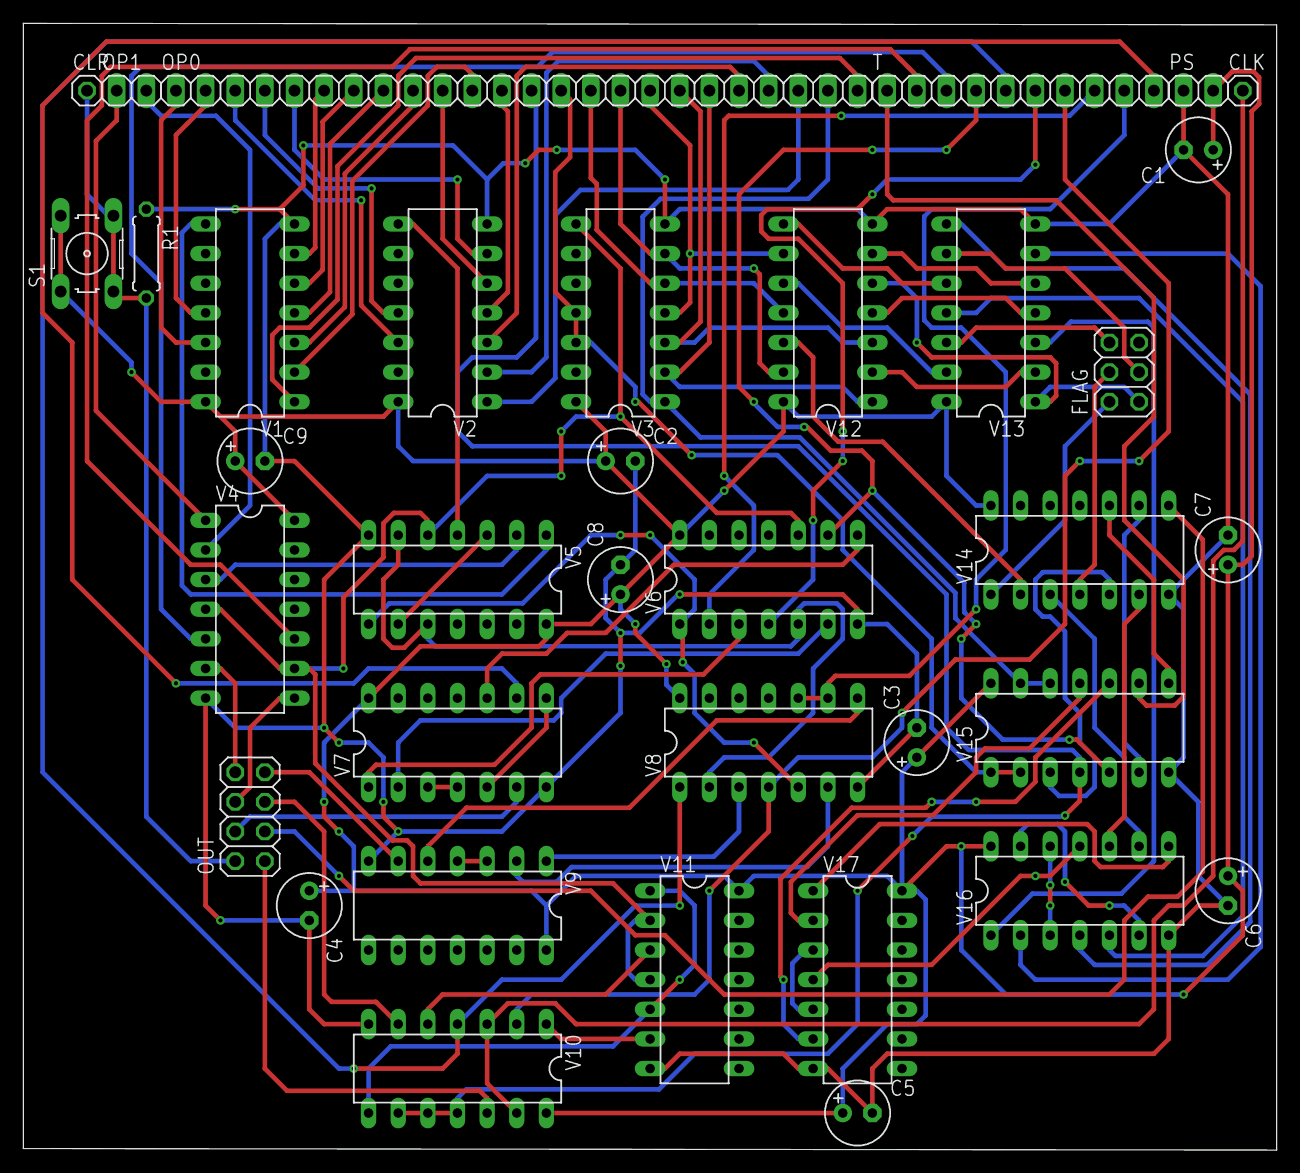
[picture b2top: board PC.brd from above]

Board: 2 copper layers, 107.4 x 96.6 mm, 36 parts (0 on the bottom side), 93 nets.
